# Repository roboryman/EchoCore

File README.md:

# EchoCore

A USB-powered, two-channel, low-noise acquisition board for biopotentials (EEG/ECG). Two differential inputs with a shared reference go through a high-impedance analog front end into a 24-bit delta-sigma ADC at 64× gain, and the samples stream to a computer over USB. An onboard IMU records motion for artifact removal.

## Specs

- 2 differential channels, shared reference
- 24-bit ΔΣ ADC (TI ADS131M02), 64× gain, 250 SPS per channel
- 0.42 µVrms input-referred noise (datasheet)
- ~1–100 Hz band, >100 MΩ input impedance
- USB 2.0 Full Speed (CDC) over USB-C, bus-powered
- 6-DOF IMU

> Not a medical device. The inputs are not isolated from USB.

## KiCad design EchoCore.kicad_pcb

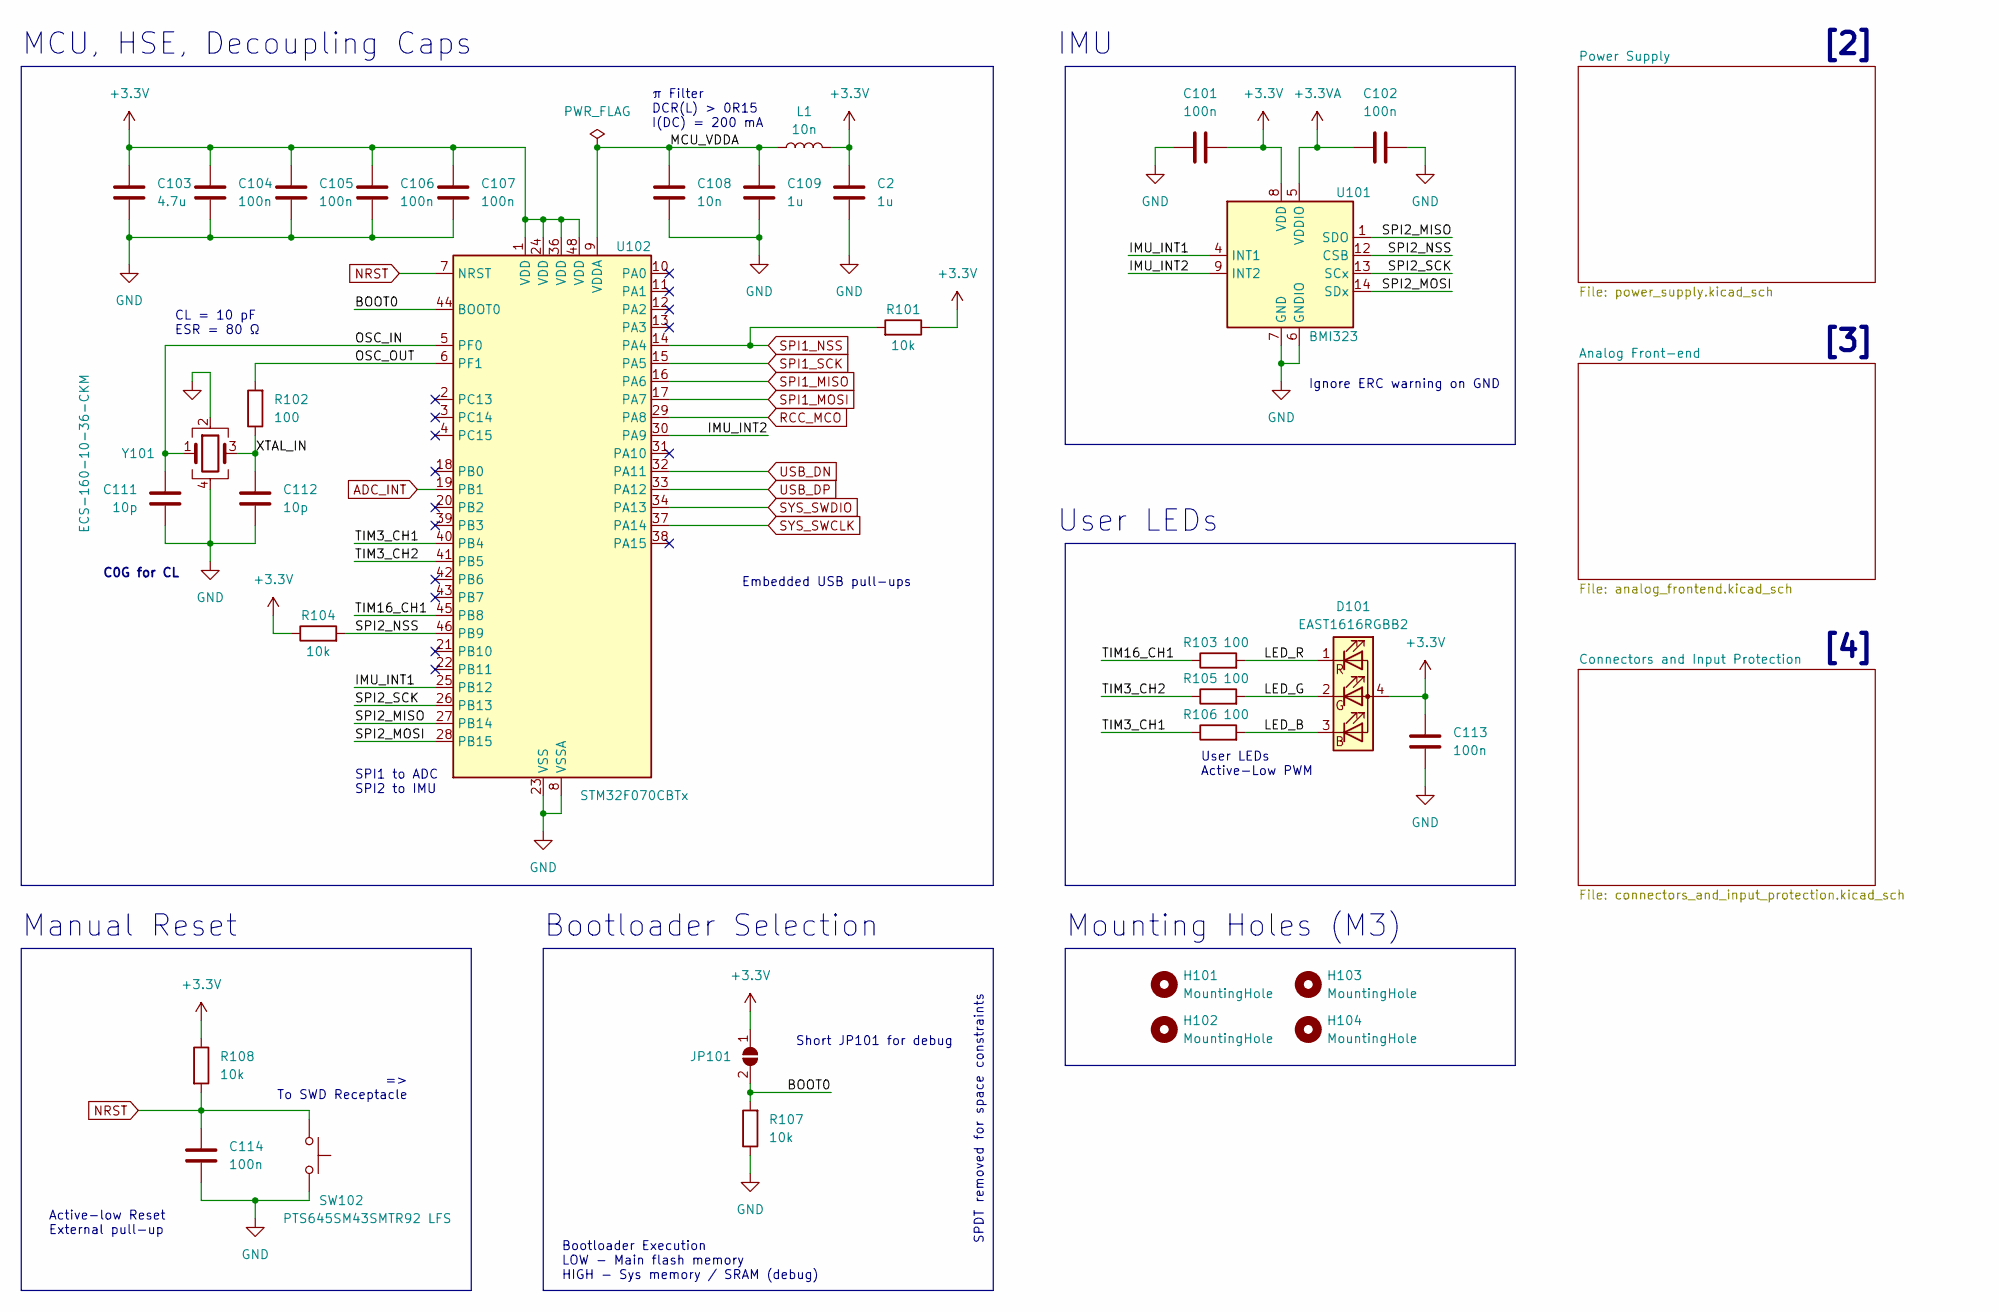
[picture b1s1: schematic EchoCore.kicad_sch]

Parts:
C2, C109: 1u; C_0603_1608Metric; Manufacturer Part Number CL10B105KP8NNNC; JLCPCB Part Number C15849
C101, C102, C104, C105, C106, C107, C113, C114: 100n; C_0402_1005Metric; Manufacturer Part Number CL05B104KA5NNNC; JLCPCB Part Number C1525
C103: 4.7u; C_0603_1608Metric; Manufacturer Part Number CL10B475KQ8NQNC; JLCPCB Part Number C19666
C108: 10n; C_0402_1005Metric; Manufacturer Part Number GRM1555C1E103GE01D
C111, C112: 10p; C_0805_2012Metric; Manufacturer Part Number CL21C100CBANNNC
D101: EAST1616RGBB2; EAST1616RGBB2_RGBA; Manufacturer Part Number EAST1616RGBB2
H101, H102, H103, H104: MountingHole; MountingHole_3.2mm_M3
JP101: SolderJumper_2_Open; SolderJumper-2_P1.3mm_Open_RoundedPad1.0x1.5mm
L1: 10n; L_0402_1005Metric; Manufacturer Part Number LQG15WZ10NH02D
R101, R104, R107, R108: 10k; R_0603_1608Metric; Manufacturer Part Number CRCW060310K0FKEAHP; JLCPCB Part Number C25804
R102, R103, R105, R106: 100; R_0402_1005Metric; Manufacturer Part Number CRCW0402100RFKEDHP; JLCPCB Part Number C25076
SW102: PTS645SM43SMTR92 LFS; SW_SPST_PTS645; Manufacturer Part Number PTS645SM43SMTR92LFS
U101: BMI323; Bosch_LGA-14_3x2.5mm_P0.5mm; Manufacturer Part Number BMI323
U102: STM32F070CBTx; LQFP-48_7x7mm_P0.5mm; Manufacturer Part Number STM32F070CBT6
Y101: ECS-160-10-36-CKM; Crystal_SMD_ECS_ECX-2236-4Pin_2.5x2.0mm; Manufacturer Part Number ECS-160-10-36-CKM-TR3

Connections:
+3.3V: C101.2, C103.1, C104.1, C105.1, C106.1, C107.1, C113.1, D101.4 (A), JP101.1 (A), R101.1, R104.1, R108.1, U101.8 (VDD), U102.1 (VDD), U102.24 (VDD), U102.36 (VDD), U102.48 (VDD); also elsewhere on the board
+3.3VA: C102.1, U101.5 (VDDIO); also elsewhere on the board
/BOOT0: JP101.2 (B), R107.2, U102.44 (BOOT0)
/IMU_INT1: U101.4 (INT1), U102.25 (PB12)
/IMU_INT2: U101.9 (INT2), U102.30 (PA9)
/LED_B: D101.3 (BK), R106.2
/LED_G: D101.2 (GK), R105.2
/LED_R: D101.1 (RK), R103.2
/MCU_VDDA: C108.1, C109.1, U102.9 (VDDA); also elsewhere on the board
/OSC_IN: C111.1, U102.5 (PF0), Y101.1
/OSC_OUT: R102.2, U102.6 (PF1)
/SPI2_MISO: U101.1 (SDO), U102.27 (PB14)
/SPI2_MOSI: U101.14 (SDx), U102.28 (PB15)
/SPI2_NSS: R104.2, U101.12 (CSB), U102.46 (PB9)
/SPI2_SCK: U101.13 (SCx), U102.26 (PB13)
/TIM3_CH1: R106.1, U102.40 (PB4)
/TIM3_CH2: R105.1, U102.41 (PB5)
/TIM16_CH1: R103.1, U102.45 (PB8)
/XTAL_IN: C112.1, R102.1, Y101.3
ADC_INT: U102.19 (PB1); also elsewhere on the board
GND: C101.1, C102.2, C103.2, C104.2, C105.2, C106.2, C107.2, C108.2, C109.2, C111.2, C112.2, C113.2, C114.2, R107.1, SW102.2, U101.6 (GNDIO), U101.7 (GND), U102.8 (VSSA), U102.23 (VSS), U102.35 (VSS), U102.47 (VSS), Y101.2, Y101.4; also elsewhere on the board
NRST: C114.1, R108.2, SW102.1, U102.7 (NRST); also elsewhere on the board
RCC_MCO: U102.29 (PA8); also elsewhere on the board
SPI1_MISO: U102.16 (PA6); also elsewhere on the board
SPI1_MOSI: U102.17 (PA7); also elsewhere on the board
SPI1_NSS: R101.2, U102.14 (PA4); also elsewhere on the board
SPI1_SCK: U102.15 (PA5); also elsewhere on the board
SYS_SWCLK: U102.37 (PA14); also elsewhere on the board
SYS_SWDIO: U102.34 (PA13); also elsewhere on the board
USB_DN: U102.32 (PA11); also elsewhere on the board
USB_DP: U102.33 (PA12); also elsewhere on the board

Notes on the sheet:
Bootloader Selection
CL = 10 pF ESR = 80 Ω
IMU
Bootloader Execution LOW - Main flash memory HIGH - Sys memory / SRAM (debug)
SPDT removed for space constraints
Manual Reset
π Filter DCR(L) > 0R15 I(DC) = 200 mA
User LEDs Active-Low PWM
Ignore ERC warning on GND
[4]
SPI1 to ADC SPI2 to IMU
[3]
[2]
Mounting Holes (M3)
User LEDs
Embedded USB pull-ups
Short JP101 for debug
C0G for CL
Active-low Reset External pull-up
MCU, HSE, Decoupling Caps
=> To SWD Receptacle

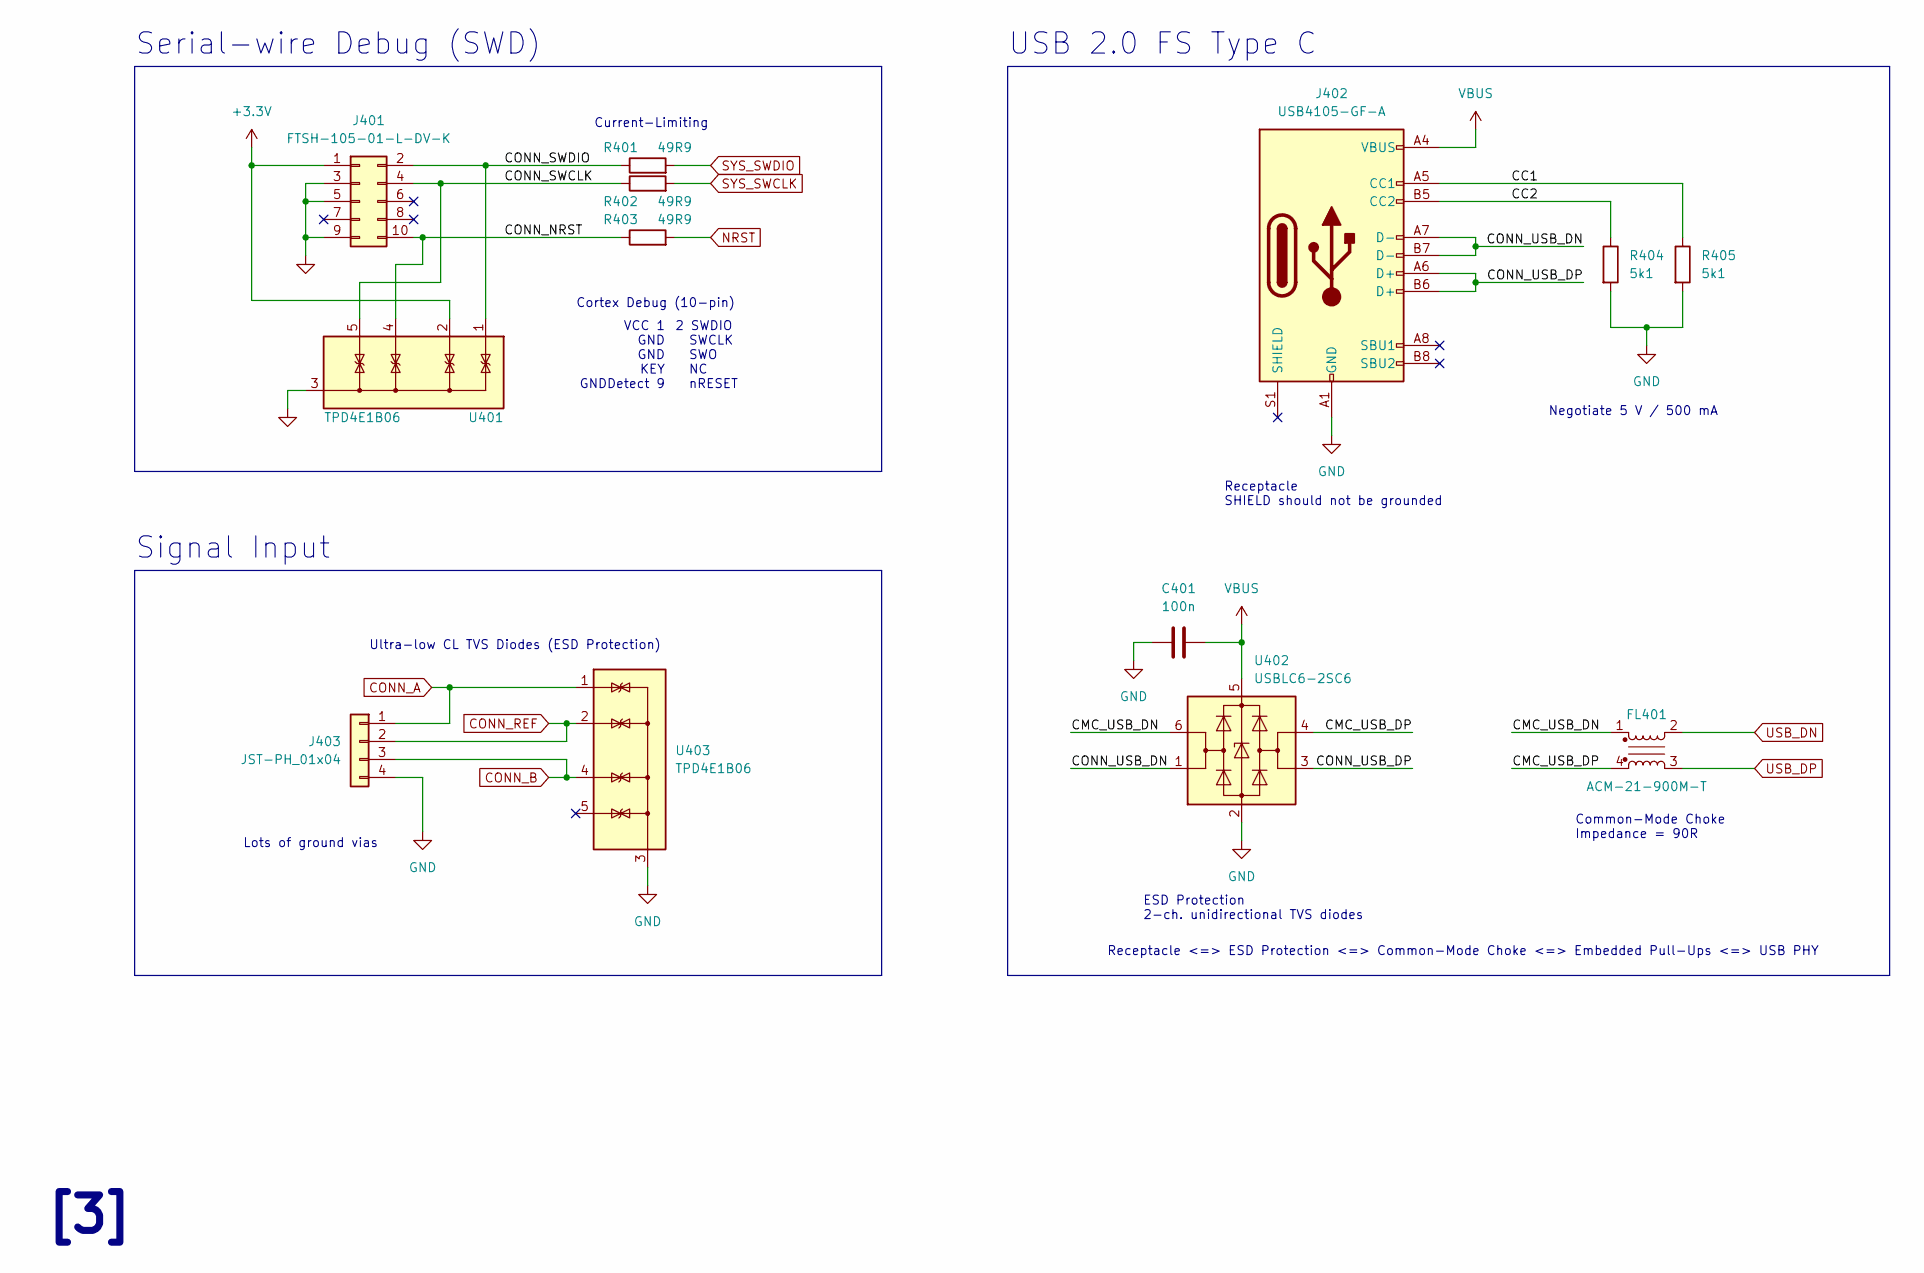
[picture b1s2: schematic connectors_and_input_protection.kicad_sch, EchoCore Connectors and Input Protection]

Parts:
C401: 100n; C_0402_1005Metric; Manufacturer Part Number CL05B104KA5NNNC; JLCPCB Part Number C1525
FL401: ACM-21-900M-T; ABRACON_ACM-21-900M-T; Manufacturer Part Number ACM-21-900M-T
J401: FTSH-105-01-L-DV-K; SAMTEC_FTSH-105-01-L-DV-K; Manufacturer Part Number FTSH-105-01-L-DV-K
J402: USB4105-GF-A; USB_C_Receptacle_GCT_USB4105-xx-A_16P_TopMnt_Horizontal; Manufacturer Part Number USB4105-GF-A
J403: JST-PH_01x04; JST_PH_S4B-PH-K_1x04_P2.00mm_Horizontal; Manufacturer Part Number S4B-PH-K-S
R401, R402, R403: 49R9; R_0402_1005Metric; Manufacturer Part Number RC0402FR-0749R9L; JLCPCB Part Number C25120
R404, R405: 5k1; R_0603_1608Metric; Manufacturer Part Number RC0603FR-135K1L; JLCPCB Part Number C23186
U401, U403: TPD4E1B06; SOT-363_SC-70-6; Manufacturer Part Number TPD4E1B06DCKR
U402: USBLC6-2SC6; SOT-23-6; Manufacturer Part Number USBLC6-2SC6

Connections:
+3.3V: J401.1, U401.2 (IO2); also elsewhere on the board
/Connectors and Input Protection/CC1: J402.A5 (CC1), R405.1
/Connectors and Input Protection/CC2: J402.B5 (CC2), R404.1
/Connectors and Input Protection/CMC_USB_DN: FL401.1, U402.6 (I/O1)
/Connectors and Input Protection/CMC_USB_DP: FL401.4, U402.4 (I/O2)
/Connectors and Input Protection/CONN_NRST: J401.10, R403.1, U401.4 (IO3)
/Connectors and Input Protection/CONN_SWCLK: J401.4, R402.1, U401.5 (IO4)
/Connectors and Input Protection/CONN_SWDIO: J401.2, R401.1, U401.1 (IO1)
/Connectors and Input Protection/CONN_USB_DN: J402.A7 (D-), J402.B7 (D-), U402.1 (I/O1)
/Connectors and Input Protection/CONN_USB_DP: J402.A6 (D+), J402.B6 (D+), U402.3 (I/O2)
CONN_A: J403.1, U403.1 (IO1); also elsewhere on the board
CONN_B: J403.3, U403.4 (IO3); also elsewhere on the board
CONN_REF: J403.2, U403.2 (IO2); also elsewhere on the board
GND: C401.1, J401.3, J401.5, J401.9, J402.A1 (GND), J402.A12 (GND), J402.B1 (GND), J402.B12 (GND), J403.4, R404.2, R405.2, U401.3 (GND), U402.2 (GND), U403.3 (GND); also elsewhere on the board
NRST: R403.2; also elsewhere on the board
SYS_SWCLK: R402.2; also elsewhere on the board
SYS_SWDIO: R401.2; also elsewhere on the board
USB_DN: FL401.2; also elsewhere on the board
USB_DP: FL401.3; also elsewhere on the board
VBUS: C401.2, J402.A4 (VBUS), J402.A9 (VBUS), J402.B4 (VBUS), J402.B9 (VBUS), U402.5 (VBUS); also elsewhere on the board

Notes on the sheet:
USB 2.0 FS Type C
Receptacle SHIELD should not be grounded
2 SWDIO SWCLK SWO NC nRESET
Signal Input
Ultra-low CL TVS Diodes (ESD Protection)
Serial-wire Debug (SWD)
Common-Mode Choke Impedance = 90R
Negotiate 5 V / 500 mA
Cortex Debug (10-pin)
Lots of ground vias
[3]
Current-Limiting
Receptacle <=> ESD Protection <=> Common-Mode Choke <=> Embedded Pull-Ups <=> USB PHY
ESD Protection 2-ch. unidirectional TVS diodes
VCC 1 GND GND KEY GNDDetect 9

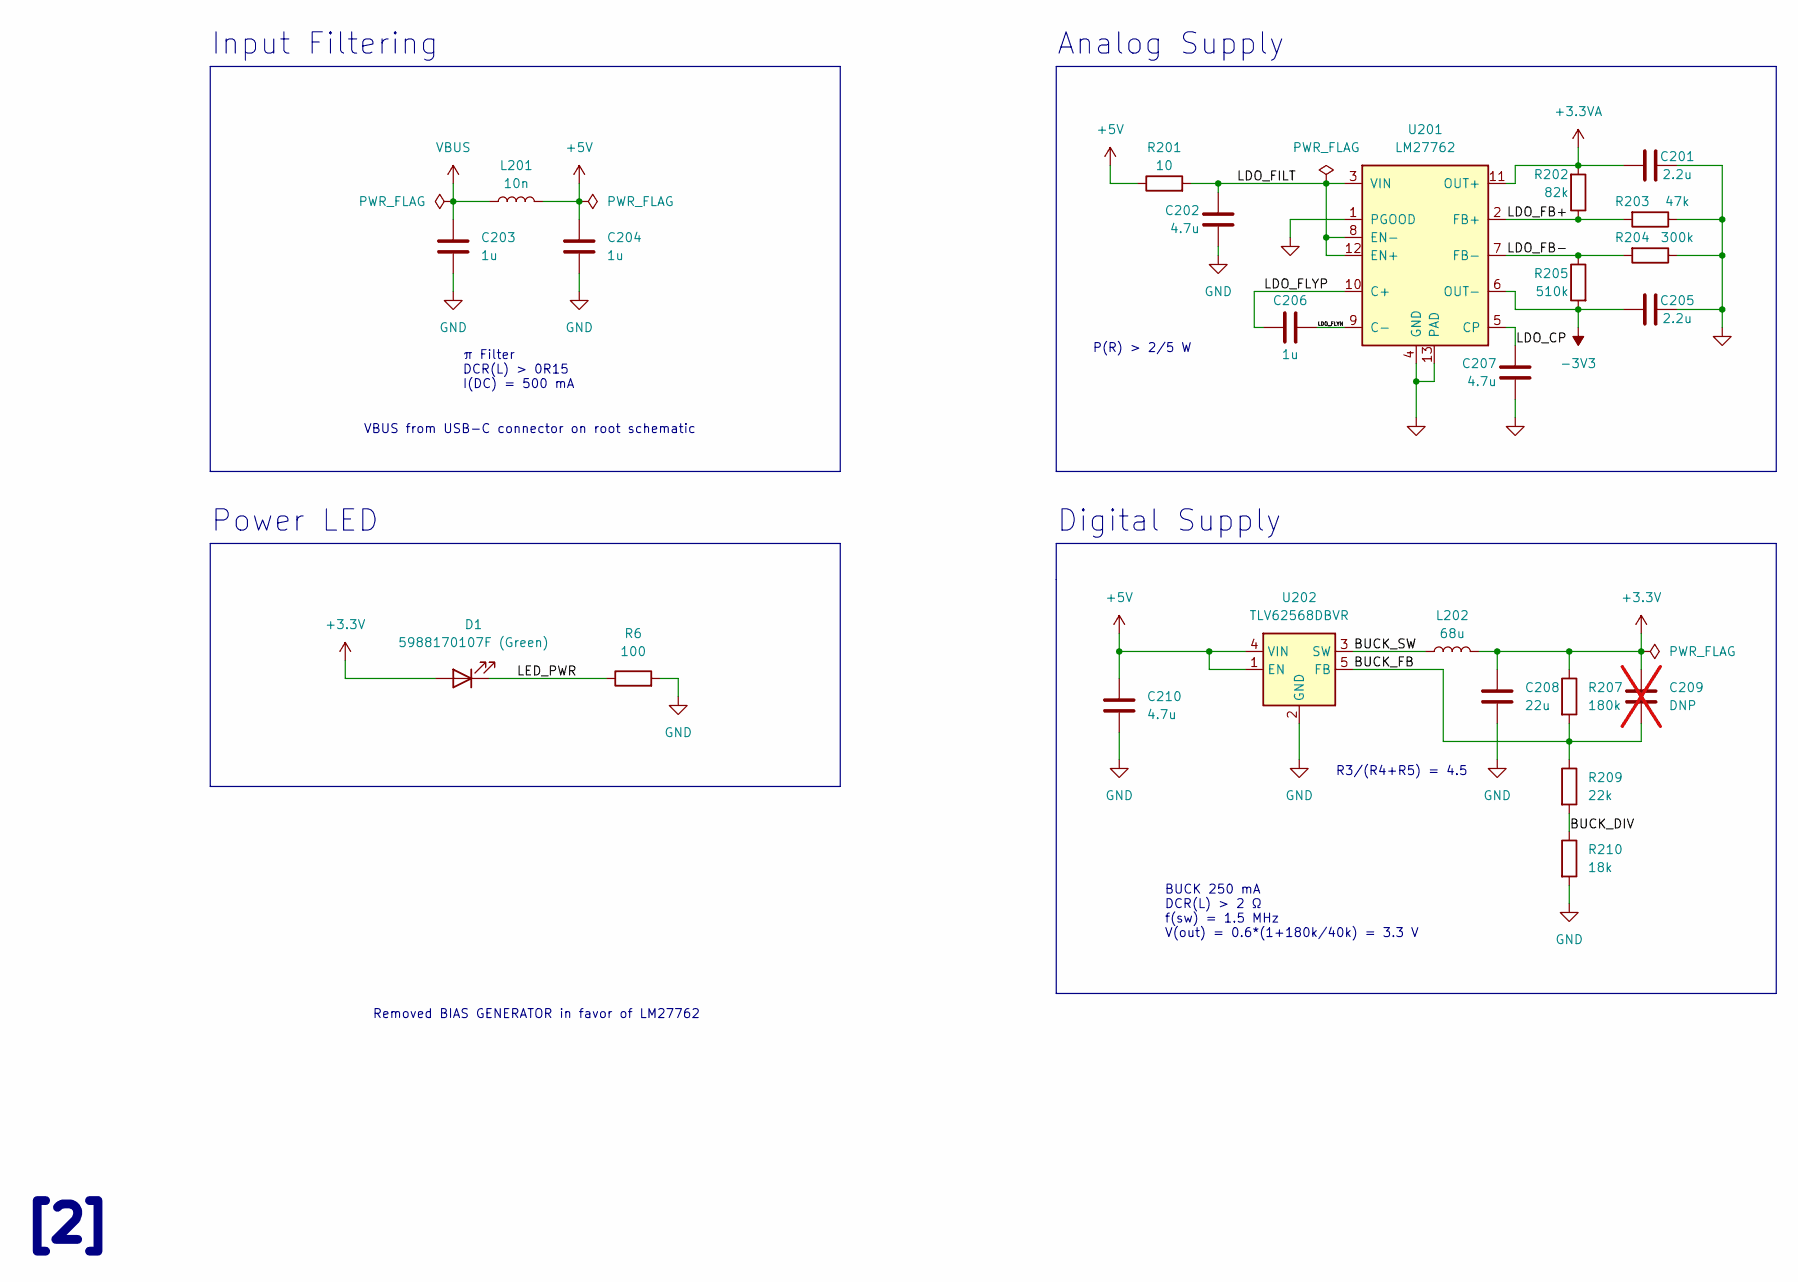
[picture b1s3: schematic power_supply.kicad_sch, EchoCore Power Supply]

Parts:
C201, C205: 2.2u; C_0603_1608Metric; Manufacturer Part Number CL10B225KP8NNNC; JLCPCB Part Number C23630
C202, C207, C210: 4.7u; C_0603_1608Metric; Manufacturer Part Number CL10B475KQ8NQNC; JLCPCB Part Number C19666
C203, C204, C206: 1u; C_0603_1608Metric; Manufacturer Part Number CL10B105KP8NNNC; JLCPCB Part Number C15849
C208: 22u; C_0805_2012Metric; Manufacturer Part Number CL21A226KQCLRNC; JLCPCB Part Number C45783
C209: DNP; C_0805_2012Metric; not fitted
D1: 5988170107F (Green); DIALIGHT_598-81xx; Manufacturer Part Number 5988170107F
L201: 10n; L_0402_1005Metric; Manufacturer Part Number LQG15WZ10NH02D
L202: 68u; TDK_VLS3015CX-H; Manufacturer Part Number VLS3015CX-680M-H
R6: 100; R_0402_1005Metric; Manufacturer Part Number CRCW0402100RFKEDHP; JLCPCB Part Number C25076
R201: 10; R_0805_2012Metric; Manufacturer Part Number ESR10EZPJ100; JLCPCB Part Number C17415
R202: 82k; R_0603_1608Metric; Manufacturer Part Number CRGP0603F82K; JLCPCB Part Number C23254
R203: 47k; R_0805_2012Metric; Manufacturer Part Number CRCW080547K0FKEAHP; JLCPCB Part Number C17713
R204: 300k; R_0805_2012Metric; Manufacturer Part Number RCS0805300KFKEA; JLCPCB Part Number C17616
R205: 510k; R_0805_2012Metric; Manufacturer Part Number ERJ-PB6B5103V; JLCPCB Part Number C17733
R207: 180k; R_0805_2012Metric; Manufacturer Part Number ERJ-UP6F1803V; JLCPCB Part Number C17501
R209: 22k; R_0603_1608Metric; Manufacturer Part Number ERJ-PA3F2202V; JLCPCB Part Number C31850
R210: 18k; R_0603_1608Metric; Manufacturer Part Number ERJ-PA3F1802V; JLCPCB Part Number C25810
U201: LM27762; WSON-12-1EP_3x2mm_P0.5mm_EP1x2.65; Manufacturer Part Number LM27762DSSR
U202: TLV62568DBVR; SOT-23-5; Manufacturer Part Number TLV62568DBVR

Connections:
+3.3V: C208.2, C209.2, L202.2, R207.1; also elsewhere on the board
+3.3VA: C201.1, R202.2, U201.11 (OUT+); also elsewhere on the board
+5V: C204.1, C210.1, L201.2, R201.1, U202.1 (EN), U202.4 (VIN)
-3V3: C205.1, R205.2, U201.6 (OUT-); also elsewhere on the board
/Power Supply/BUCK_DIV: R209.2, R210.1
/Power Supply/BUCK_FB: C209.1, R207.2, R209.1, U202.5 (FB)
/Power Supply/BUCK_SW: L202.1, U202.3 (SW)
/Power Supply/LDO_CP: C207.1, U201.5 (CP)
/Power Supply/LDO_FB+: R202.1, R203.2, U201.2 (FB+)
/Power Supply/LDO_FB-: R204.2, R205.1, U201.7 (FB-)
/Power Supply/LDO_FILT: C202.1, R201.2, U201.3 (VIN), U201.8 (EN-), U201.12 (EN+)
/Power Supply/LDO_FLYN: C206.2, U201.9 (C-)
/Power Supply/LDO_FLYP: C206.1, U201.10 (C+)
GND: C201.2, C202.2, C203.2, C204.2, C205.2, C207.2, C208.1, C210.2, R203.1, R204.1, R210.2, U201.1 (PGOOD), U201.4 (GND), U201.13 (PAD), U202.2 (GND); also elsewhere on the board
VBUS: C203.1, L201.1; also elsewhere on the board

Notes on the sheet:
π Filter DCR(L) > 0R15 I(DC) = 500 mA
Digital Supply
P(R) > 2/5 W
VBUS from USB-C connector on root schematic
Analog Supply
Input Filtering
R3/(R4+R5) = 4.5
Power LED
Removed BIAS GENERATOR in favor of LM27762
BUCK 250 mA DCR(L) > 2 Ω f(sw) = 1.5 MHz V(out) = 0.6*(1+180k/40k) = 3.3 V
[2]

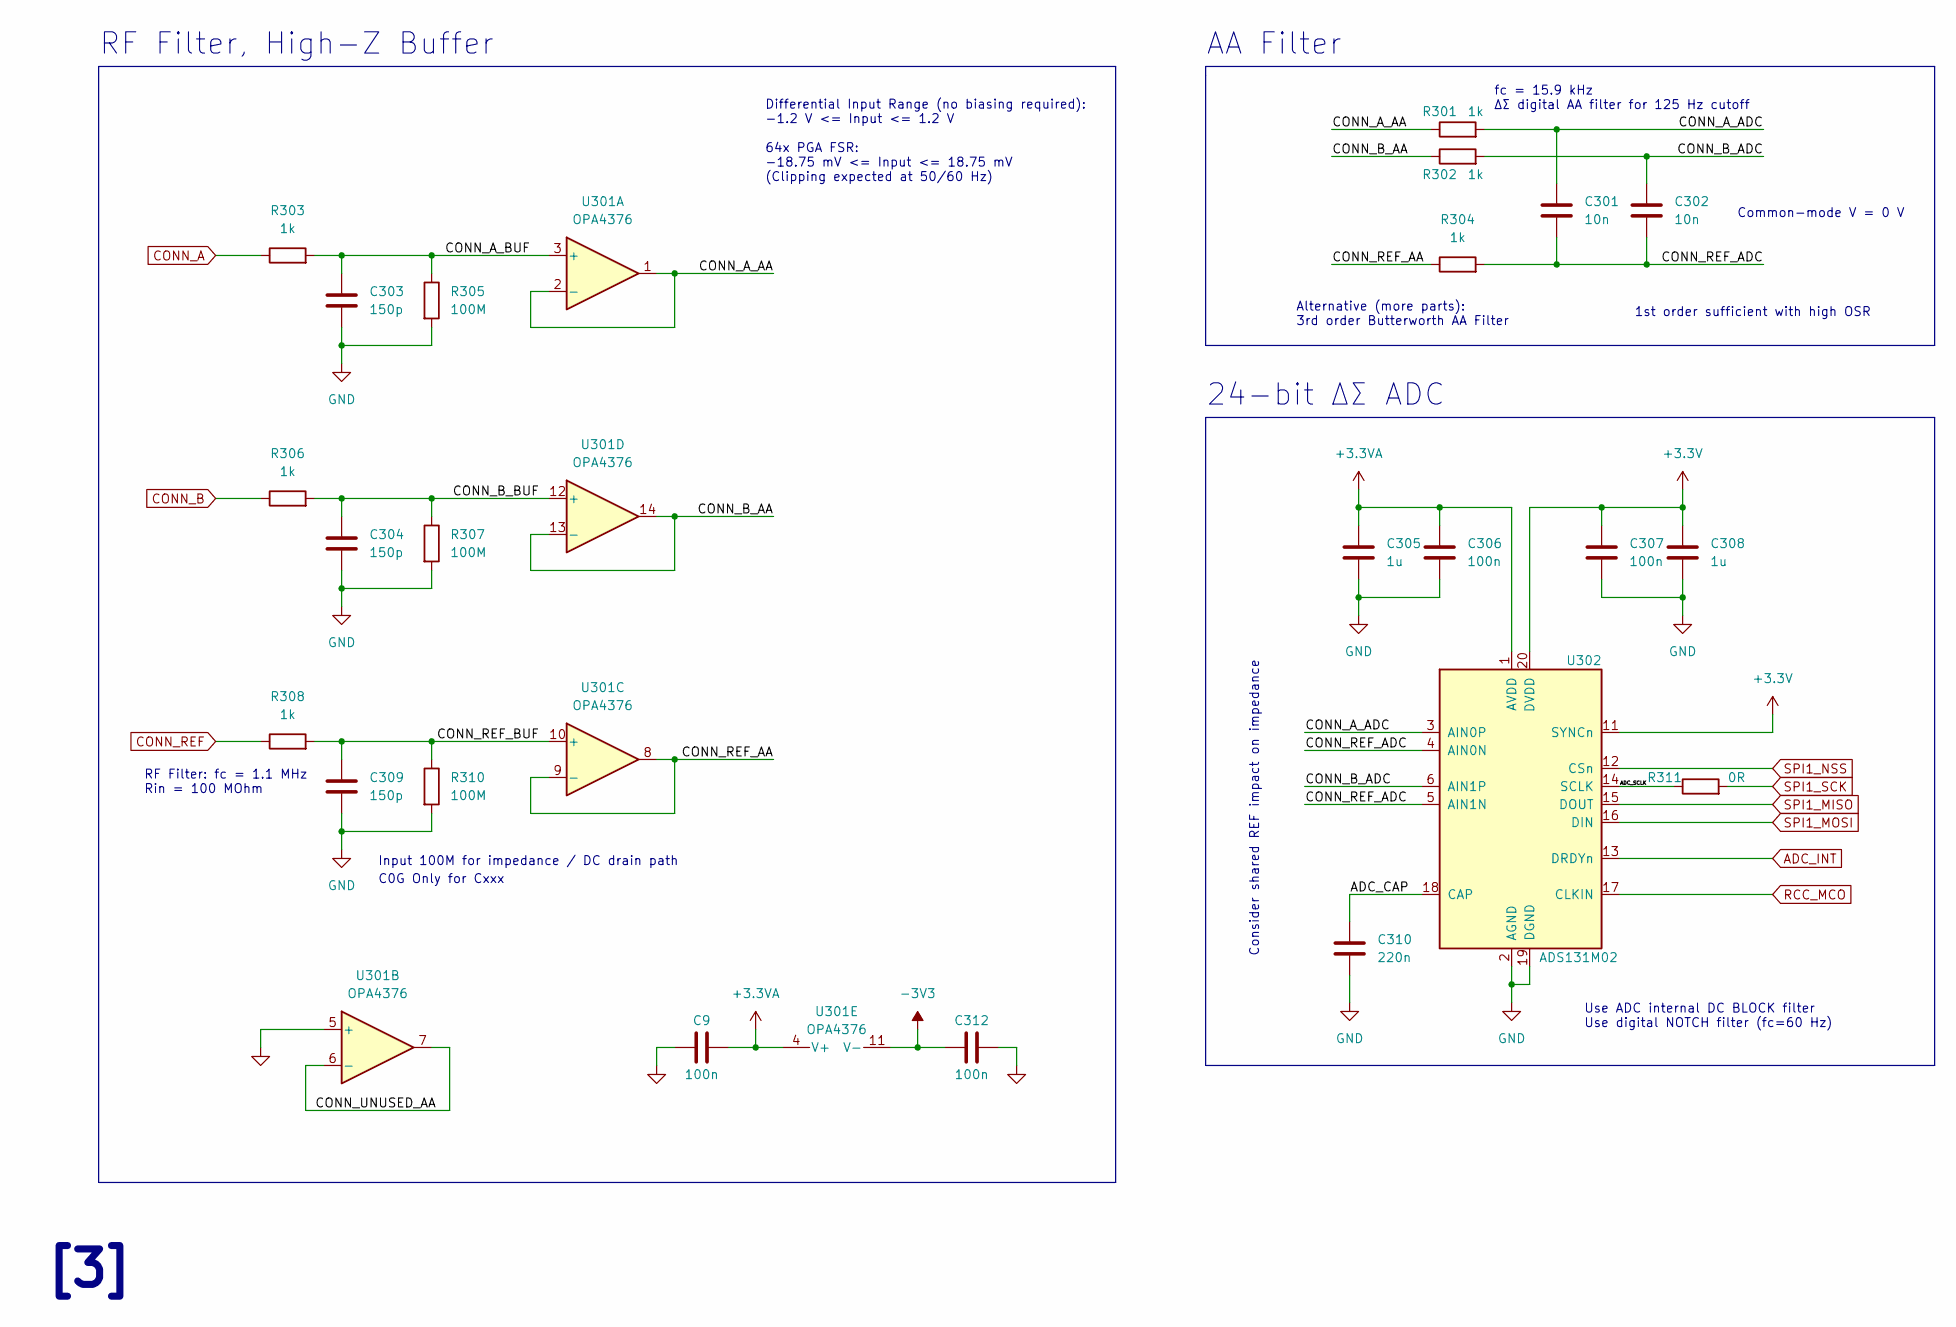
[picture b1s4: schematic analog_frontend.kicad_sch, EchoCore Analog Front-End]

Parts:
C9, C306, C307, C312: 100n; C_0402_1005Metric; Manufacturer Part Number CL05B104KA5NNNC; JLCPCB Part Number C1525
C301, C302: 10n; C_0402_1005Metric; Manufacturer Part Number GRM1555C1E103GE01D
C303, C304, C309: 150p; C_0805_2012Metric; Manufacturer Part Number CC0805FRNPO9BN151
C305, C308: 1u; C_0603_1608Metric; Manufacturer Part Number CL10B105KP8NNNC; JLCPCB Part Number C15849
C310: 220n; C_0603_1608Metric; Manufacturer Part Number GRM188R71E224JA88J
R301, R302, R303, R304, R306, R308: 1k; R_0603_1608Metric; Manufacturer Part Number RG1608P-102-B-T5; JLCPCB Part Number C21190
R305, R307, R310: 100M; R_0805_2012Metric; Manufacturer Part Number RC0805JR-13100ML
R311: 0R; R_0402_1005Metric; Manufacturer Part Number CR0402-J/-000GLF; JLCPCB Part Number C17168
U301: OPA4376; TSSOP-14_4.4x5mm_P0.65mm; Manufacturer Part Number OPA4376AIPW
U302: ADS131M02; TSSOP-20_4.4x6.5mm_P0.65mm; Manufacturer Part Number ADS131M02IPWT

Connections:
+3.3V: C307.2, C308.1, U302.11 (SYNCn), U302.20 (DVDD); also elsewhere on the board
+3.3VA: C305.1, C306.2, U301.4 (V+), U302.1 (AVDD); also elsewhere on the board
-3V3: C312.1, U301.11 (V-); also elsewhere on the board
/Analog Front-end/ADC_CAP: C310.1, U302.18 (CAP)
/Analog Front-end/ADC_SCLK: R311.1, U302.14 (SCLK)
/Analog Front-end/CONN_A_AA: R301.1, U301.1, U301.2 (-)
/Analog Front-end/CONN_A_ADC: C301.1, R301.2, U302.3 (AIN0P)
/Analog Front-end/CONN_A_BUF: C303.1, R303.2, R305.1, U301.3 (+)
/Analog Front-end/CONN_B_AA: R302.1, U301.13 (-), U301.14
/Analog Front-end/CONN_B_ADC: C302.1, R302.2, U302.6 (AIN1P)
/Analog Front-end/CONN_B_BUF: C304.1, R306.2, R307.1, U301.12 (+)
/Analog Front-end/CONN_REF_AA: R304.1, U301.8, U301.9 (-)
/Analog Front-end/CONN_REF_ADC: C301.2, C302.2, R304.2, U302.4 (AIN0N), U302.5 (AIN1N)
/Analog Front-end/CONN_REF_BUF: C309.1, R308.2, R310.1, U301.10 (+)
/Analog Front-end/CONN_UNUSED_AA: U301.6 (-), U301.7
ADC_INT: U302.13 (DRDYn); also elsewhere on the board
CONN_A: R303.1; also elsewhere on the board
CONN_B: R306.1; also elsewhere on the board
CONN_REF: R308.1; also elsewhere on the board
GND: C303.2, C304.2, C305.2, C306.1, C307.1, C308.2, C309.2, C310.2, C312.2, R305.2, R307.2, R310.2, U301.5 (+), U302.2 (AGND), U302.19 (DGND); also elsewhere on the board
RCC_MCO: U302.17 (CLKIN); also elsewhere on the board
SPI1_MISO: U302.15 (DOUT); also elsewhere on the board
SPI1_MOSI: U302.16 (DIN); also elsewhere on the board
SPI1_NSS: U302.12 (CSn); also elsewhere on the board
SPI1_SCK: R311.2; also elsewhere on the board

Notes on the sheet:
1st order sufficient with high OSR
24-bit ΔΣ ADC
Differential Input Range (no biasing required): -1.2 V <= Input <= 1.2 V 64x PGA FSR: -18.75 mV <= Input <= 18.75 mV (Clipping expected at 50/60 Hz)
C0G Only for Cxxx
Use ADC internal DC BLOCK filter Use digital NOTCH filter (fc=60 Hz)
Input 100M for impedance / DC drain path
[3]
Alternative (more parts): 3rd order Butterworth AA Filter
AA Filter
Common-mode V = 0 V
Consider shared REF impact on impedance
RF Filter, High-Z Buffer
fc = 15.9 kHz ΔΣ digital AA filter for 125 Hz cutoff
RF Filter: fc = 1.1 MHz Rin = 100 MOhm

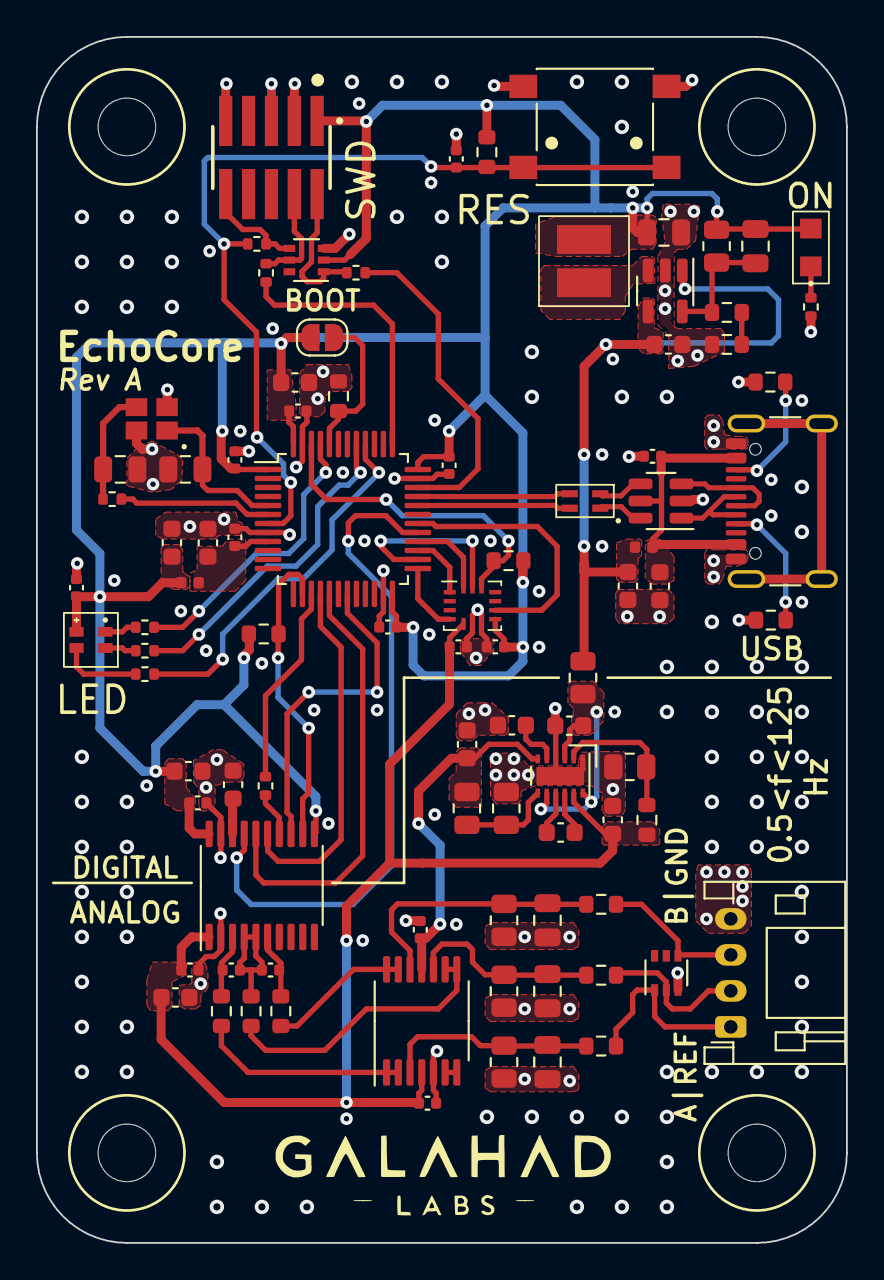
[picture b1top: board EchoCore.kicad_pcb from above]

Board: 4 copper layers, 45.0 x 67.0 mm, 94 parts (0 on the bottom side), 68 nets.

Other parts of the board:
C110: 1u; C_0603_1608Metric
C311: 100n; C_0402_1005Metric
D201: 5988170107F (Green); DIALIGHT_598-81xx
L101: 10n; L_0402_1005Metric
R206: 100; R_0402_1005Metric

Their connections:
+3.3V: C110.1, D201.2 (A), L101.2; also elsewhere on the board
+3.3VA: C311.1; also elsewhere on the board
/MCU_VDDA: L101.1; also elsewhere on the board
/Power Supply/LED_PWR: D201.1 (K), R206.1
GND: C110.2, C311.2, R206.2; also elsewhere on the board

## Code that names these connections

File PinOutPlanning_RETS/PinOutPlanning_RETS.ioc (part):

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Mcu.Name=STM32F070CBTx
Mcu.Package=LQFP48
Mcu.UserName=STM32F070CBTx
PA11.Mode=Device
PA11.Signal=USB_DM
PA12.Mode=Device
PA12.Signal=USB_DP
PA13.Mode=Serial_Wire
PA13.Signal=SYS_SWDIO
PA14.Mode=Serial_Wire
PA14.Signal=SYS_SWCLK
PA4.Mode=NSS_Signal_Hard_Output
PA4.Signal=SPI1_NSS
PA5.Mode=Full_Duplex_Master
PA5.Signal=SPI1_SCK
PA6.Mode=Full_Duplex_Master
PA6.Signal=SPI1_MISO
PA7.Mode=Full_Duplex_Master
PA7.Signal=SPI1_MOSI
PA8.Mode=Clock-out
PA8.Signal=RCC_MCO
PA9.GPIOParameters=GPIO_Label
PA9.GPIO_Label=IMU_INT2
PA9.Signal=GPXTI9
PB1.GPIOParameters=GPIO_Label
PB1.GPIO_Label=ADC_INT
PB1.Signal=GPXTI1
PB12.GPIOParameters=GPIO_Label
PB12.GPIO_Label=IMU_INT1
PB12.Signal=GPXTI12
PB13.Mode=Full_Duplex_Master
PB13.Signal=SPI2_SCK
PB14.Mode=Full_Duplex_Master
PB14.Signal=SPI2_MISO
PB15.Mode=Full_Duplex_Master
PB15.Signal=SPI2_MOSI
PB4.Signal=S_TIM3_CH1
PB5.Signal=S_TIM3_CH2
PB8.Signal=S_TIM16_CH1
PB9.GPIOParameters=GPIO_Label
PB9.GPIO_Label=SPI2_CS
PB9.Signal=GPIO_Output
PF0-OSC_IN.Mode=HSE-External-Oscillator
PF0-OSC_IN.Signal=RCC_OSC_IN
PF1-OSC_OUT.Mode=HSE-External-Oscillator
PF1-OSC_OUT.Signal=RCC_OSC_OUT
RCC.HSE_VALUE=16000000
RCC.SYSCLKFreq_VALUE=48000000
RCC.SYSCLKSource=RCC_SYSCLKSOURCE_PLLCLK
board=custom

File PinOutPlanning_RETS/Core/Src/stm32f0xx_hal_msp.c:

/* USER CODE BEGIN Header */
/**
  ******************************************************************************
  * @file         stm32f0xx_hal_msp.c
  * @brief        This file provides code for the MSP Initialization
  *               and de-Initialization codes.
  ******************************************************************************
  * @attention
  *
  * Copyright (c) 2023 STMicroelectronics.
  * All rights reserved.
  *
  * This software is licensed under terms that can be found in the LICENSE file
  * in the root directory of this software component.
  * If no LICENSE file comes with this software, it is provided AS-IS.
  *
  ******************************************************************************
  */
/* USER CODE END Header */

/* Includes ------------------------------------------------------------------*/
#include "main.h"

/* USER CODE BEGIN Includes */

/* USER CODE END Includes */

/* Private typedef -----------------------------------------------------------*/
/* USER CODE BEGIN TD */

/* USER CODE END TD */

/* Private define ------------------------------------------------------------*/
/* USER CODE BEGIN Define */

/* USER CODE END Define */

/* Private macro -------------------------------------------------------------*/
/* USER CODE BEGIN Macro */

/* USER CODE END Macro */

/* Private variables ---------------------------------------------------------*/
/* USER CODE BEGIN PV */

/* USER CODE END PV */

/* Private function prototypes -----------------------------------------------*/
/* USER CODE BEGIN PFP */

/* USER CODE END PFP */

/* External functions --------------------------------------------------------*/
/* USER CODE BEGIN ExternalFunctions */

/* USER CODE END ExternalFunctions */

/* USER CODE BEGIN 0 */

/* USER CODE END 0 */

void HAL_TIM_MspPostInit(TIM_HandleTypeDef *htim);
                                        /**
  * Initializes the Global MSP.
  */
void HAL_MspInit(void)
{
  /* USER CODE BEGIN MspInit 0 */

  /* USER CODE END MspInit 0 */

  __HAL_RCC_SYSCFG_CLK_ENABLE();
  __HAL_RCC_PWR_CLK_ENABLE();

  /* System interrupt init*/

  /* USER CODE BEGIN MspInit 1 */

  /* USER CODE END MspInit 1 */
}

/**
* @brief SPI MSP Initialization
* This function configures the hardware resources used in this example
* @param hspi: SPI handle pointer
* @retval None
*/
void HAL_SPI_MspInit(SPI_HandleTypeDef* hspi)
{
  GPIO_InitTypeDef GPIO_InitStruct = {0};
  if(hspi->Instance==SPI1)
  {
  /* USER CODE BEGIN SPI1_MspInit 0 */

  /* USER CODE END SPI1_MspInit 0 */
    /* Peripheral clock enable */
    __HAL_RCC_SPI1_CLK_ENABLE();

    __HAL_RCC_GPIOA_CLK_ENABLE();
    /**SPI1 GPIO Configuration
    PA4     ------> SPI1_NSS
    PA5     ------> SPI1_SCK
    PA6     ------> SPI1_MISO
    PA7     ------> SPI1_MOSI
    */
    GPIO_InitStruct.Pin = GPIO_PIN_4|GPIO_PIN_5|GPIO_PIN_6|GPIO_PIN_7;
    GPIO_InitStruct.Mode = GPIO_MODE_AF_PP;
    GPIO_InitStruct.Pull = GPIO_NOPULL;
    GPIO_InitStruct.Speed = GPIO_SPEED_FREQ_HIGH;
    GPIO_InitStruct.Alternate = GPIO_AF0_SPI1;
    HAL_GPIO_Init(GPIOA, &GPIO_InitStruct);

  /* USER CODE BEGIN SPI1_MspInit 1 */

  /* USER CODE END SPI1_MspInit 1 */
  }
  else if(hspi->Instance==SPI2)
  {
  /* USER CODE BEGIN SPI2_MspInit 0 */

  /* USER CODE END SPI2_MspInit 0 */
    /* Peripheral clock enable */
    __HAL_RCC_SPI2_CLK_ENABLE();

    __HAL_RCC_GPIOB_CLK_ENABLE();
    /**SPI2 GPIO Configuration
    PB13     ------> SPI2_SCK
    PB14     ------> SPI2_MISO
    PB15     ------> SPI2_MOSI
    */
    GPIO_InitStruct.Pin = GPIO_PIN_13|GPIO_PIN_14|GPIO_PIN_15;
    GPIO_InitStruct.Mode = GPIO_MODE_AF_PP;
    GPIO_InitStruct.Pull = GPIO_NOPULL;
    GPIO_InitStruct.Speed = GPIO_SPEED_FREQ_HIGH;
    GPIO_InitStruct.Alternate = GPIO_AF0_SPI2;
    HAL_GPIO_Init(GPIOB, &GPIO_InitStruct);

  /* USER CODE BEGIN SPI2_MspInit 1 */

  /* USER CODE END SPI2_MspInit 1 */
  }

}

/**
* @brief SPI MSP De-Initialization
* This function freeze the hardware resources used in this example
* @param hspi: SPI handle pointer
* @retval None
*/
void HAL_SPI_MspDeInit(SPI_HandleTypeDef* hspi)
{
  if(hspi->Instance==SPI1)
  {
  /* USER CODE BEGIN SPI1_MspDeInit 0 */

  /* USER CODE END SPI1_MspDeInit 0 */
    /* Peripheral clock disable */
    __HAL_RCC_SPI1_CLK_DISABLE();

    /**SPI1 GPIO Configuration
    PA4     ------> SPI1_NSS
    PA5     ------> SPI1_SCK
    PA6     ------> SPI1_MISO
    PA7     ------> SPI1_MOSI
    */
    HAL_GPIO_DeInit(GPIOA, GPIO_PIN_4|GPIO_PIN_5|GPIO_PIN_6|GPIO_PIN_7);

  /* USER CODE BEGIN SPI1_MspDeInit 1 */

  /* USER CODE END SPI1_MspDeInit 1 */
  }
  else if(hspi->Instance==SPI2)
  {
  /* USER CODE BEGIN SPI2_MspDeInit 0 */

  /* USER CODE END SPI2_MspDeInit 0 */
    /* Peripheral clock disable */
    __HAL_RCC_SPI2_CLK_DISABLE();

    /**SPI2 GPIO Configuration
    PB13     ------> SPI2_SCK
    PB14     ------> SPI2_MISO
    PB15     ------> SPI2_MOSI
    */
    HAL_GPIO_DeInit(GPIOB, GPIO_PIN_13|GPIO_PIN_14|GPIO_PIN_15);

  /* USER CODE BEGIN SPI2_MspDeInit 1 */

  /* USER CODE END SPI2_MspDeInit 1 */
  }

}

/**
* @brief TIM_PWM MSP Initialization
* This function configures the hardware resources used in this example
* @param htim_pwm: TIM_PWM handle pointer
* @retval None
*/
void HAL_TIM_PWM_MspInit(TIM_HandleTypeDef* htim_pwm)
{
  if(htim_pwm->Instance==TIM3)
  {
  /* USER CODE BEGIN TIM3_MspInit 0 */

  /* USER CODE END TIM3_MspInit 0 */
    /* Peripheral clock enable */
    __HAL_RCC_TIM3_CLK_ENABLE();
  /* USER CODE BEGIN TIM3_MspInit 1 */

  /* USER CODE END TIM3_MspInit 1 */
  }

}

/**
* @brief TIM_Base MSP Initialization
* This function configures the hardware resources used in this example
* @param htim_base: TIM_Base handle pointer
* @retval None
*/
void HAL_TIM_Base_MspInit(TIM_HandleTypeDef* htim_base)
{
  if(htim_base->Instance==TIM16)
  {
  /* USER CODE BEGIN TIM16_MspInit 0 */

  /* USER CODE END TIM16_MspInit 0 */
    /* Peripheral clock enable */
    __HAL_RCC_TIM16_CLK_ENABLE();
  /* USER CODE BEGIN TIM16_MspInit 1 */

  /* USER CODE END TIM16_MspInit 1 */
  }

}

void HAL_TIM_MspPostInit(TIM_HandleTypeDef* htim)
{
  GPIO_InitTypeDef GPIO_InitStruct = {0};
  if(htim->Instance==TIM3)
  {
  /* USER CODE BEGIN TIM3_MspPostInit 0 */

  /* USER CODE END TIM3_MspPostInit 0 */
    __HAL_RCC_GPIOB_CLK_ENABLE();
    /**TIM3 GPIO Configuration
    PB4     ------> TIM3_CH1
    PB5     ------> TIM3_CH2
    */
    GPIO_InitStruct.Pin = GPIO_PIN_4|GPIO_PIN_5;
    GPIO_InitStruct.Mode = GPIO_MODE_AF_PP;
    GPIO_InitStruct.Pull = GPIO_NOPULL;
    GPIO_InitStruct.Speed = GPIO_SPEED_FREQ_LOW;
    GPIO_InitStruct.Alternate = GPIO_AF1_TIM3;
    HAL_GPIO_Init(GPIOB, &GPIO_InitStruct);

  /* USER CODE BEGIN TIM3_MspPostInit 1 */

  /* USER CODE END TIM3_MspPostInit 1 */
  }
  else if(htim->Instance==TIM16)
  {
  /* USER CODE BEGIN TIM16_MspPostInit 0 */

  /* USER CODE END TIM16_MspPostInit 0 */

    __HAL_RCC_GPIOB_CLK_ENABLE();
    /**TIM16 GPIO Configuration
    PB8     ------> TIM16_CH1
    */
    GPIO_InitStruct.Pin = GPIO_PIN_8;
    GPIO_InitStruct.Mode = GPIO_MODE_AF_PP;
    GPIO_InitStruct.Pull = GPIO_NOPULL;
    GPIO_InitStruct.Speed = GPIO_SPEED_FREQ_LOW;
    GPIO_InitStruct.Alternate = GPIO_AF2_TIM16;
    HAL_GPIO_Init(GPIOB, &GPIO_InitStruct);

  /* USER CODE BEGIN TIM16_MspPostInit 1 */

  /* USER CODE END TIM16_MspPostInit 1 */
  }

}
/**
* @brief TIM_PWM MSP De-Initialization
* This function freeze the hardware resources used in this example
* @param htim_pwm: TIM_PWM handle pointer
* @retval None
*/
void HAL_TIM_PWM_MspDeInit(TIM_HandleTypeDef* htim_pwm)
{
  if(htim_pwm->Instance==TIM3)
  {
  /* USER CODE BEGIN TIM3_MspDeInit 0 */

  /* USER CODE END TIM3_MspDeInit 0 */
    /* Peripheral clock disable */
    __HAL_RCC_TIM3_CLK_DISABLE();
  /* USER CODE BEGIN TIM3_MspDeInit 1 */

  /* USER CODE END TIM3_MspDeInit 1 */
  }

}

/**
* @brief TIM_Base MSP De-Initialization
* This function freeze the hardware resources used in this example
* @param htim_base: TIM_Base handle pointer
* @retval None
*/
void HAL_TIM_Base_MspDeInit(TIM_HandleTypeDef* htim_base)
{
  if(htim_base->Instance==TIM16)
  {
  /* USER CODE BEGIN TIM16_MspDeInit 0 */

  /* USER CODE END TIM16_MspDeInit 0 */
    /* Peripheral clock disable */
    __HAL_RCC_TIM16_CLK_DISABLE();
  /* USER CODE BEGIN TIM16_MspDeInit 1 */

  /* USER CODE END TIM16_MspDeInit 1 */
  }

}

/* USER CODE BEGIN 1 */

/* USER CODE END 1 */
